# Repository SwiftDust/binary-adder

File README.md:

# Binary adder in an Airbus Beluga-shaped PCB

This is a simple binary adder in the form of an Airbus Beluga. It is a simple project for me to learn how to use ICs. This is for [Resolution Week 3](https://github.com/SwiftDust/Resolution) but a new rule states you can't use monorepos so that's why I made this separate repository.

I used the well-known 555 and CD4060 to make this PCB. I used the 555 in monostable mode with a time constant of 0.125 seconds. This is derived by the fact that the average person would click on a button no more than eight times in a second, so a time constant of 0.125 or lower is required. If we make the time constant too low, it may not be fed correctly into the 4060, so that is why I chose this value. The input of the 555 is wired to a button. The CLK input of the 4060 is then wired up with the output of the 555 and all the outputs are wired to LEDs. If the output of the 555 is high, the binary adder will add one number to the output. Additionally, I have added a "Reset" button wired to the RST input of the 4060, so people can reset the counter. I made this PCB for fun, but can be useful to learn to count in binary too!

## Schematic

## PCB design

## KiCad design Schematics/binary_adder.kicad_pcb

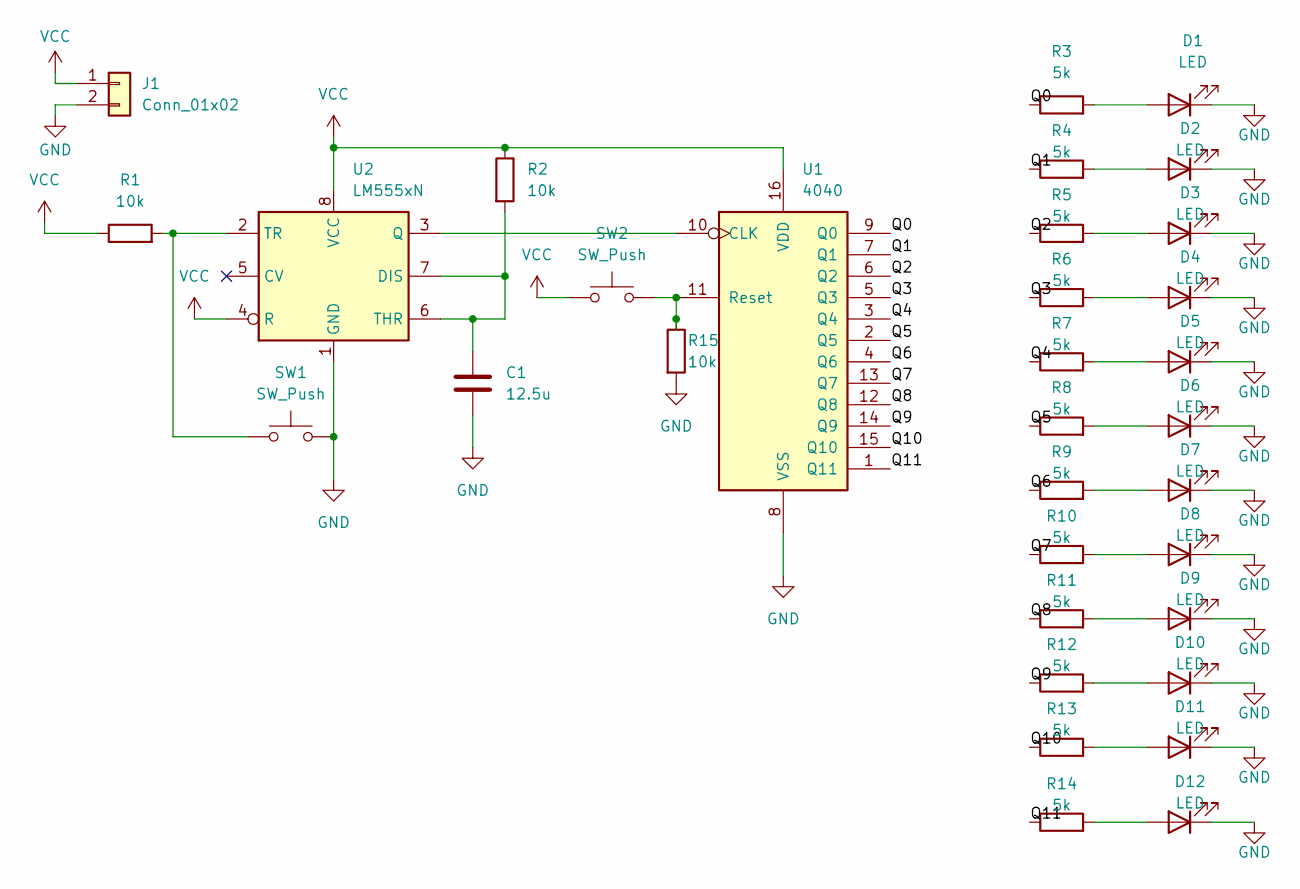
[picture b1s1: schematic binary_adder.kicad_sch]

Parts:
C1: 12.5u; C_Disc_D5.0mm_W2.5mm_P5.00mm
D1, D2, D3, D4, D5, D6, D7, D8, D9, D10, D11, D12: LED; LED_D5.0mm
J1: Conn_01x02; PinHeader_1x02_P2.54mm_Vertical
R1, R2, R15: 10k; R_Axial_DIN0204_L3.6mm_D1.6mm_P7.62mm_Horizontal
R3, R4, R5, R6, R7, R8, R9, R10, R11, R12, R13, R14: 5k; R_Axial_DIN0204_L3.6mm_D1.6mm_P7.62mm_Horizontal
SW1, SW2: SW_Push; SW_PUSH_6mm
U1: 4040; DIP-16_W7.62mm
U2: LM555xN; DIP-8_W7.62mm

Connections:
/Q0: R3.1, U1.9 (Q0)
/Q1: R4.1, U1.7 (Q1)
/Q2: R5.1, U1.6 (Q2)
/Q3: R6.1, U1.5 (Q3)
/Q4: R7.1, U1.3 (Q4)
/Q5: R8.1, U1.2 (Q5)
/Q6: R9.1, U1.4 (Q6)
/Q7: R10.1, U1.13 (Q7)
/Q8: R11.1, U1.12 (Q8)
/Q9: R12.1, U1.14 (Q9)
/Q10: R13.1, U1.15 (Q10)
/Q11: R14.1, U1.1 (Q11)
GND: C1.2, D1.1 (K), D2.1 (K), D3.1 (K), D4.1 (K), D5.1 (K), D6.1 (K), D7.1 (K), D8.1 (K), D9.1 (K), D10.1 (K), D11.1 (K), D12.1 (K), J1.2, R15.2, SW1.2, U1.8 (VSS), U2.1 (GND); also elsewhere on the board
unnamed: D1.2 (A), R3.2
unnamed: D2.2 (A), R4.2
unnamed: D3.2 (A), R5.2
unnamed: D4.2 (A), R6.2
unnamed: D5.2 (A), R7.2
unnamed: D6.2 (A), R8.2
unnamed: D7.2 (A), R9.2
unnamed: D8.2 (A), R10.2
unnamed: D9.2 (A), R11.2
unnamed: D10.2 (A), R12.2
unnamed: D11.2 (A), R13.2
unnamed: D12.2 (A), R14.2
unnamed: U1.10 (CLK), U2.3 (Q)
unnamed: R15.1, SW2.2, U1.11 (Reset)
unnamed: C1.1, R2.2, U2.6 (THR), U2.7 (DIS)
unnamed: R1.2, SW1.1, U2.2 (TR)
VCC: J1.1, R1.1, R2.1, SW2.1, U1.16 (VDD), U2.4 (R), U2.8 (VCC)

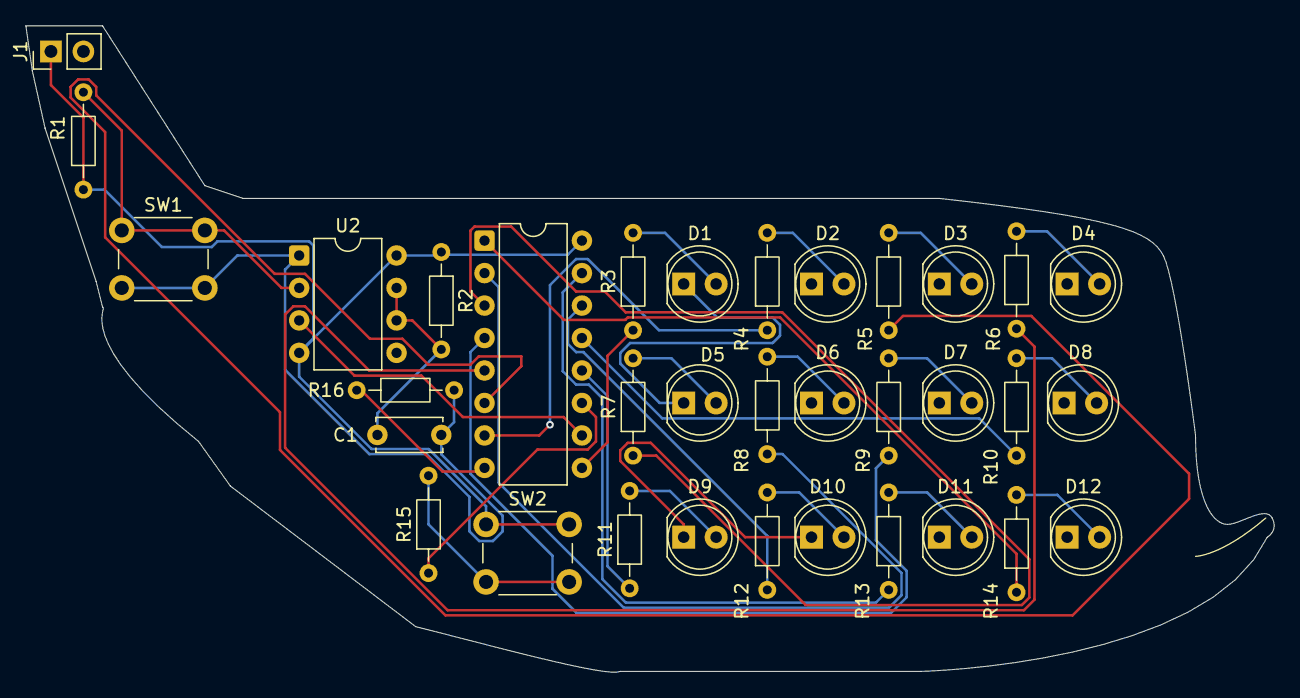
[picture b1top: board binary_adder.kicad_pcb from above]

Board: 2 copper layers, 97.7 x 50.6 mm, 34 parts (0 on the bottom side), 30 nets.

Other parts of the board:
R16: 10k; R_Axial_DIN0204_L3.6mm_D1.6mm_P7.62mm_Horizontal

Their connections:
GND: R16.2; also elsewhere on the board

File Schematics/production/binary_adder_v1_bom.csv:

Designator,Footprint,Quantity,Value,LCSC Part #
C1,C_Disc_D5.0mm_W2.5mm_P5.00mm,1,12.5u,
"D1, D10, D11, D12, D2, D3, D4, D5, D6, D7, D8, D9",LED_D5.0mm,12,LED,
"R1, R15, R2",R_Axial_DIN0204_L3.6mm_D1.6mm_P7.62mm_Horizontal,3,10k,
"R10, R11, R12, R13, R14, R3, R4, R5, R6, R7, R8, R9",R_Axial_DIN0204_L3.6mm_D1.6mm_P7.62mm_Horizontal,12,5k,
"SW1, SW2",SW_PUSH_6mm,2,SW_Push,
U1,DIP-16_W7.62mm,1,4040,
U2,DIP-8_W7.62mm,1,LM555xN,

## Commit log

2026-04-04 Add finished project
2026-04-04 Add resolution notice to README
2026-04-12 Fix GND pull resistor in schematic
    Also add ground pour
2026-06-05 Add missing power connector
2026-06-05 Add v3 gerbers
2026-06-28 Change pull down resistor
